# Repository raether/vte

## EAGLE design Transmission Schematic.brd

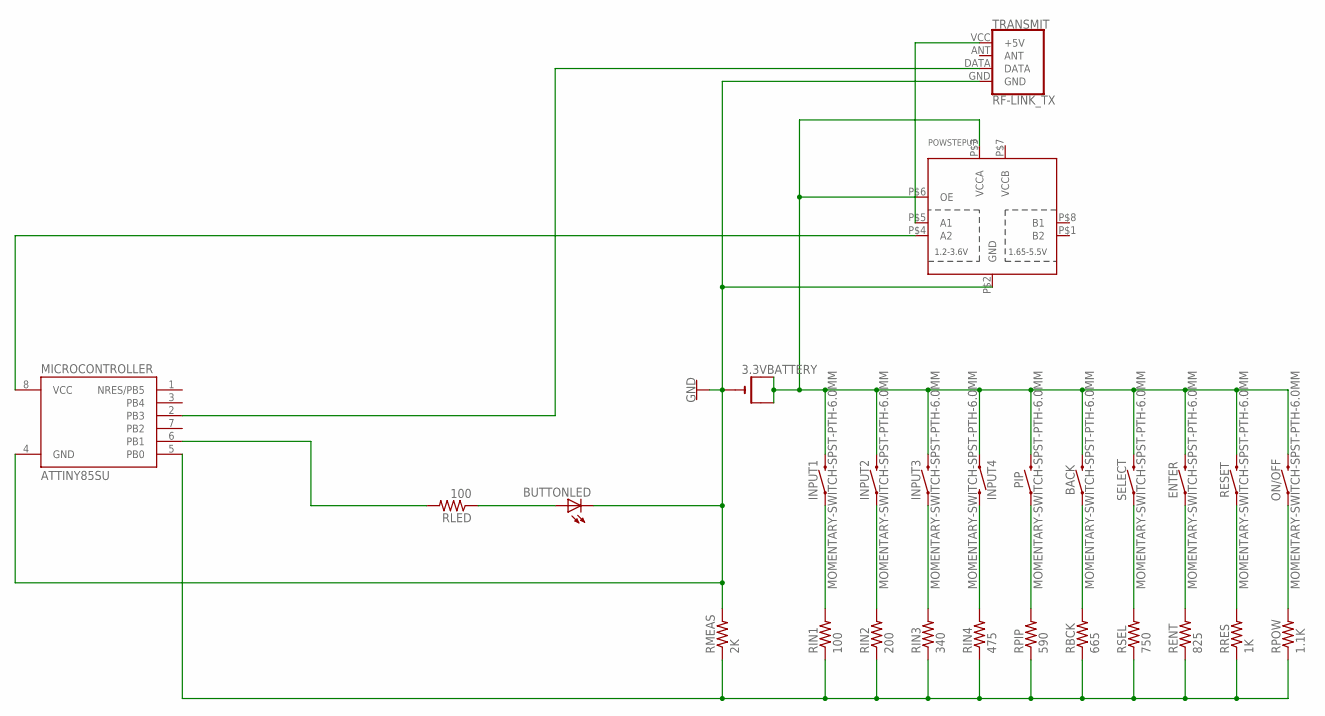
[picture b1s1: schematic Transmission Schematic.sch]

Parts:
3.3VBATTERY: CR1220THM; CR1220-THM
BACK: MOMENTARY-SWITCH-SPST-PTH-6.0MM; TACTILE_SWITCH_PTH_6.0MM
BUTTONLED: LEDCHIPLED_0805; CHIPLED_0805
ENTER: MOMENTARY-SWITCH-SPST-PTH-6.0MM; TACTILE_SWITCH_PTH_6.0MM
INPUT1, INPUT2, INPUT3, INPUT4: MOMENTARY-SWITCH-SPST-PTH-6.0MM; TACTILE_SWITCH_PTH_6.0MM
MICROCONTROLLER: ATTINY85SU; ATTINY85
ON/OFF: MOMENTARY-SWITCH-SPST-PTH-6.0MM; TACTILE_SWITCH_PTH_6.0MM
PIP: MOMENTARY-SWITCH-SPST-PTH-6.0MM; TACTILE_SWITCH_PTH_6.0MM
POWSTEPUP: TXS0102; VFSOP-8
RBCK: 665; R0805
RENT: 825; R0805
RESET: MOMENTARY-SWITCH-SPST-PTH-6.0MM; TACTILE_SWITCH_PTH_6.0MM
RIN1: 100; R0805
RIN2: 200; R0805
RIN3: 340; R0805
RIN4: 475; R0805
RLED: 100; R0805
RMEAS: 2K; R0805
RPIP: 590; R0805
RPOW: 1.1K; R0805
RRES: 1K; R0805
RSEL: 750; R0805
SELECT: MOMENTARY-SWITCH-SPST-PTH-6.0MM; TACTILE_SWITCH_PTH_6.0MM
TRANSMIT: RF-LINK_TX

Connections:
GND: 3.3VBATTERY.-, BUTTONLED.C, MICROCONTROLLER.4 (GND), POWSTEPUP.P$2 (GND), RMEAS.2, TRANSMIT.GND
unnamed: 3.3VBATTERY.+1 (+), 3.3VBATTERY.+2 (+1), BACK.3 (2), ENTER.3 (2), INPUT1.3 (2), INPUT2.3 (2), INPUT3.3 (2), INPUT4.1, ON/OFF.3 (2), PIP.3 (2), POWSTEPUP.P$3 (VCCA), POWSTEPUP.P$6 (OE), RESET.3 (2), SELECT.3 (2)
unnamed: INPUT1.1, RIN1.2
unnamed: INPUT2.1, RIN2.2
unnamed: INPUT3.1, RIN3.2
unnamed: INPUT4.3 (2), RIN4.2
unnamed: PIP.1, RPIP.2
unnamed: BACK.1, RBCK.2
unnamed: RSEL.2, SELECT.1
unnamed: ENTER.1, RENT.2
unnamed: MICROCONTROLLER.5 (PB0), RBCK.1, RENT.1, RIN1.1, RIN2.1, RIN3.1, RIN4.1, RMEAS.1, RPIP.1, RPOW.1, RRES.1, RSEL.1
unnamed: POWSTEPUP.P$5 (A1), TRANSMIT.VCC (+5V)
unnamed: MICROCONTROLLER.8 (VCC), POWSTEPUP.P$4 (A2)
unnamed: RESET.1, RRES.2
unnamed: ON/OFF.1, RPOW.2
unnamed: MICROCONTROLLER.2 (PB3), TRANSMIT.DATA
unnamed: MICROCONTROLLER.6 (PB1), RLED.2
unnamed: BUTTONLED.A, RLED.1

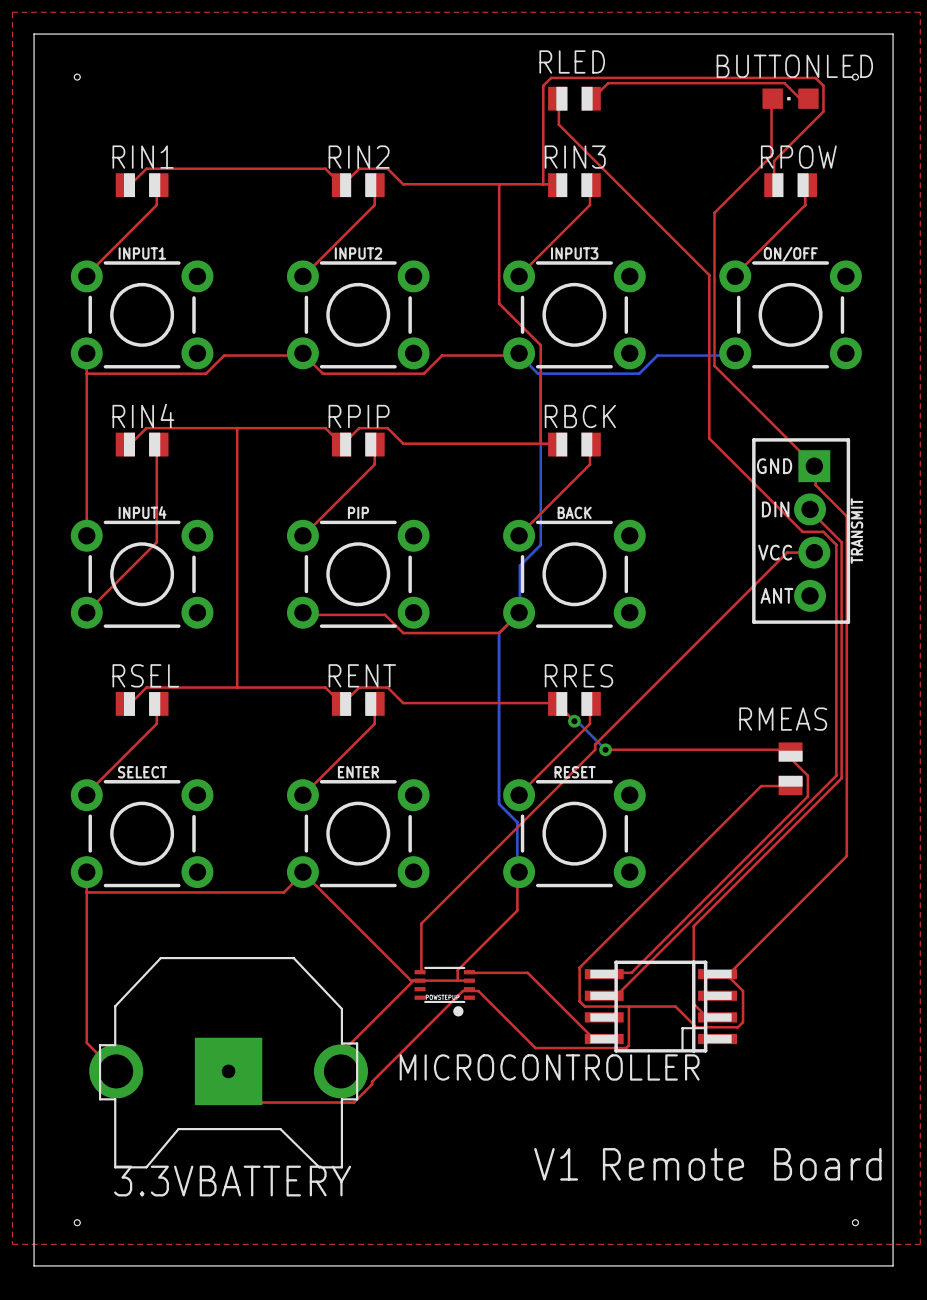
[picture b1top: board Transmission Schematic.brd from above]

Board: 2 copper layers, 50.5 x 72.4 mm, 27 parts (0 on the bottom side), 18 nets.

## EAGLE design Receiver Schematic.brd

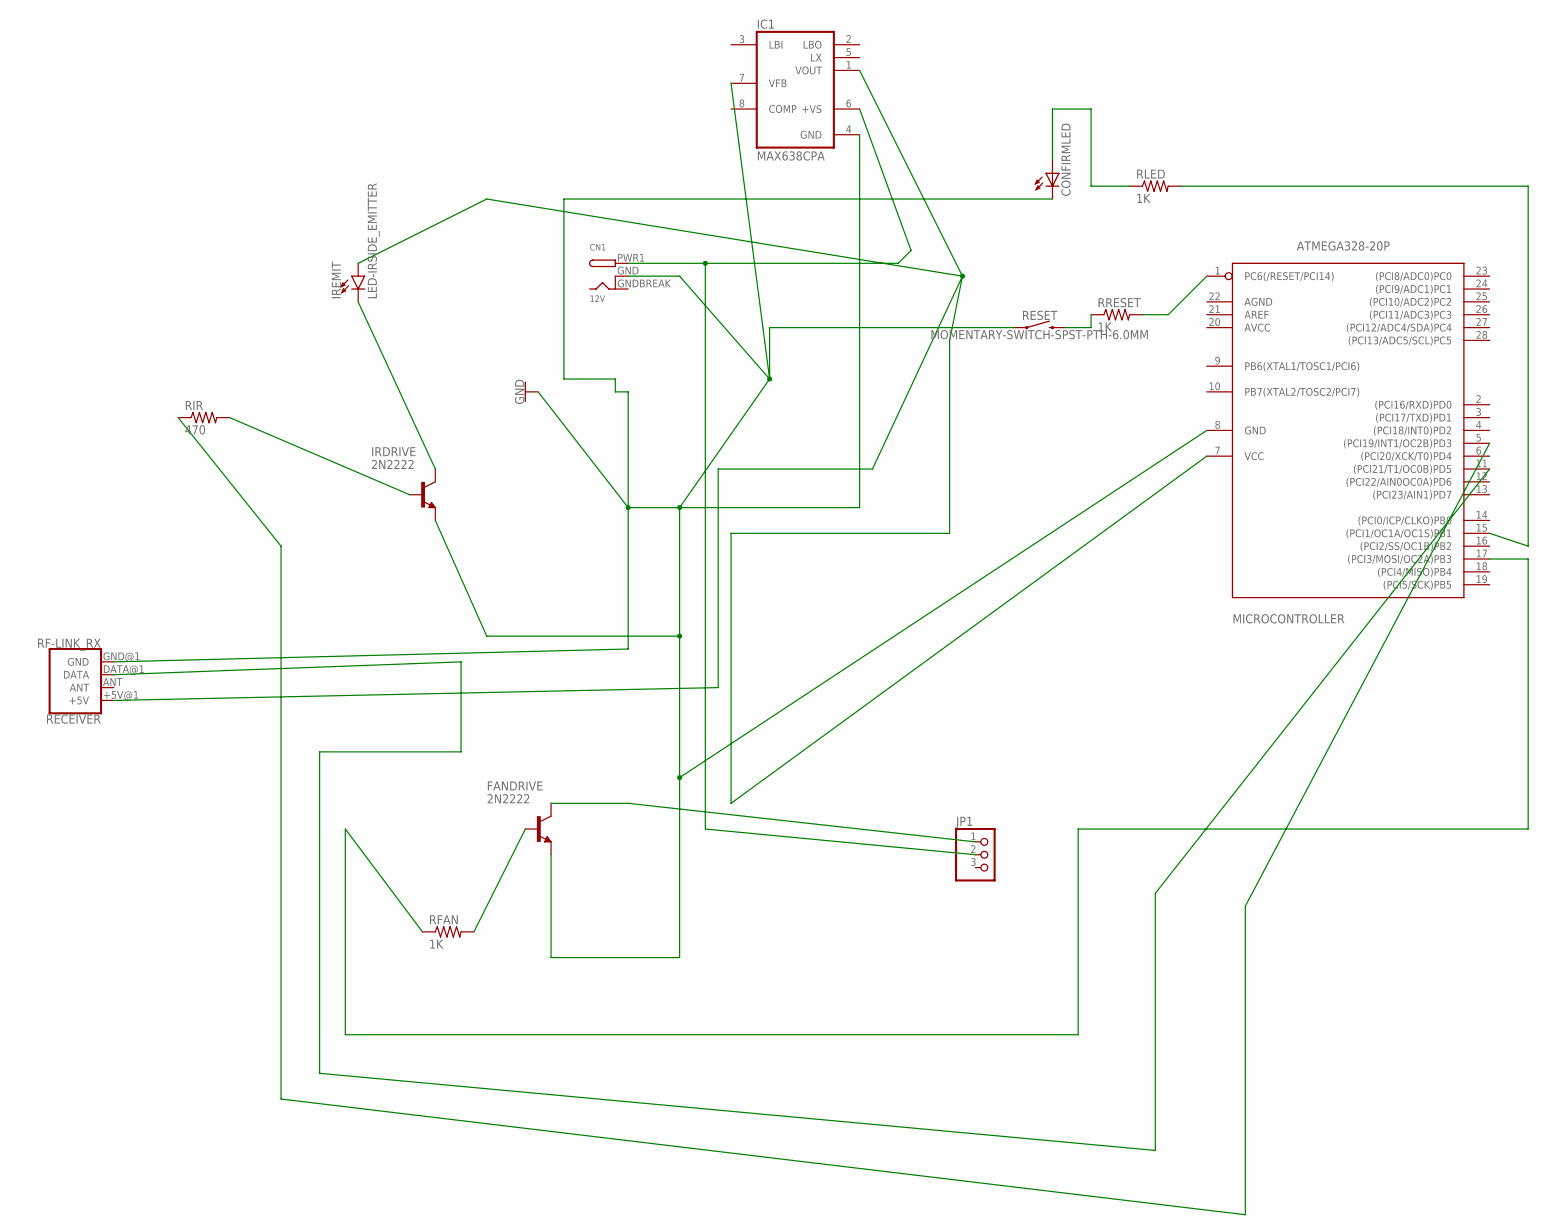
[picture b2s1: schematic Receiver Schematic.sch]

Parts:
CN1: 12V; DCJACK_2MM_SMT
CONFIRMLED: LEDCHIP-LED0805; CHIP-LED0805
FANDRIVE: 2N2222; TO92-EBC-OVAL
IC1: MAX638CPA; DIL08
IRDRIVE: 2N2222; TO92-EBC-OVAL
IREMIT: LED-IRSIDE_EMITTER; LTE-302
JP1: PINHD-1X3; 1X03
MICROCONTROLLER: ATMEGA328-20P; DIL28-3
RECEIVER: RF-LINK_RX
RESET: MOMENTARY-SWITCH-SPST-PTH-6.0MM; TACTILE_SWITCH_PTH_6.0MM
RFAN: 1K; R0805
RIR: 470; R0805
RLED: 1K; R0805
RRESET: 1K; R0805

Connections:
GND: CN1.GND (GNDBREAK), CN1.GNDBREAK (GND), CONFIRMLED.C, FANDRIVE.E, IC1.4 (GND), IC1.7 (VFB), IRDRIVE.E, MICROCONTROLLER.8 (GND), RECEIVER.GND@1 (GND), RESET.1
unnamed: IRDRIVE.C, IREMIT.C
unnamed: CN1.PWR1 (PWR), IC1.6 (+VS), JP1.2
unnamed: MICROCONTROLLER.17 ((PCI3/MOSI/OC2A)PB3), RFAN.1
unnamed: IC1.1 (VOUT), IREMIT.A, MICROCONTROLLER.7 (VCC), RECEIVER.+5V@1 (+5V)
unnamed: FANDRIVE.C, JP1.1
unnamed: IRDRIVE.B, RIR.2
unnamed: FANDRIVE.B, RFAN.2
unnamed: MICROCONTROLLER.15 ((PCI1/OC1A/OC1S)PB1), RLED.2
unnamed: MICROCONTROLLER.5 ((PCI19/INT1/OC2B)PD3), RIR.1
unnamed: MICROCONTROLLER.11 ((PCI21/T1/OC0B)PD5), RECEIVER.DATA@1 (DATA)
unnamed: CONFIRMLED.A, RLED.1
unnamed: RESET.3 (2), RRESET.1
unnamed: MICROCONTROLLER.1 (PC6(/RESET/PCI14)), RRESET.2

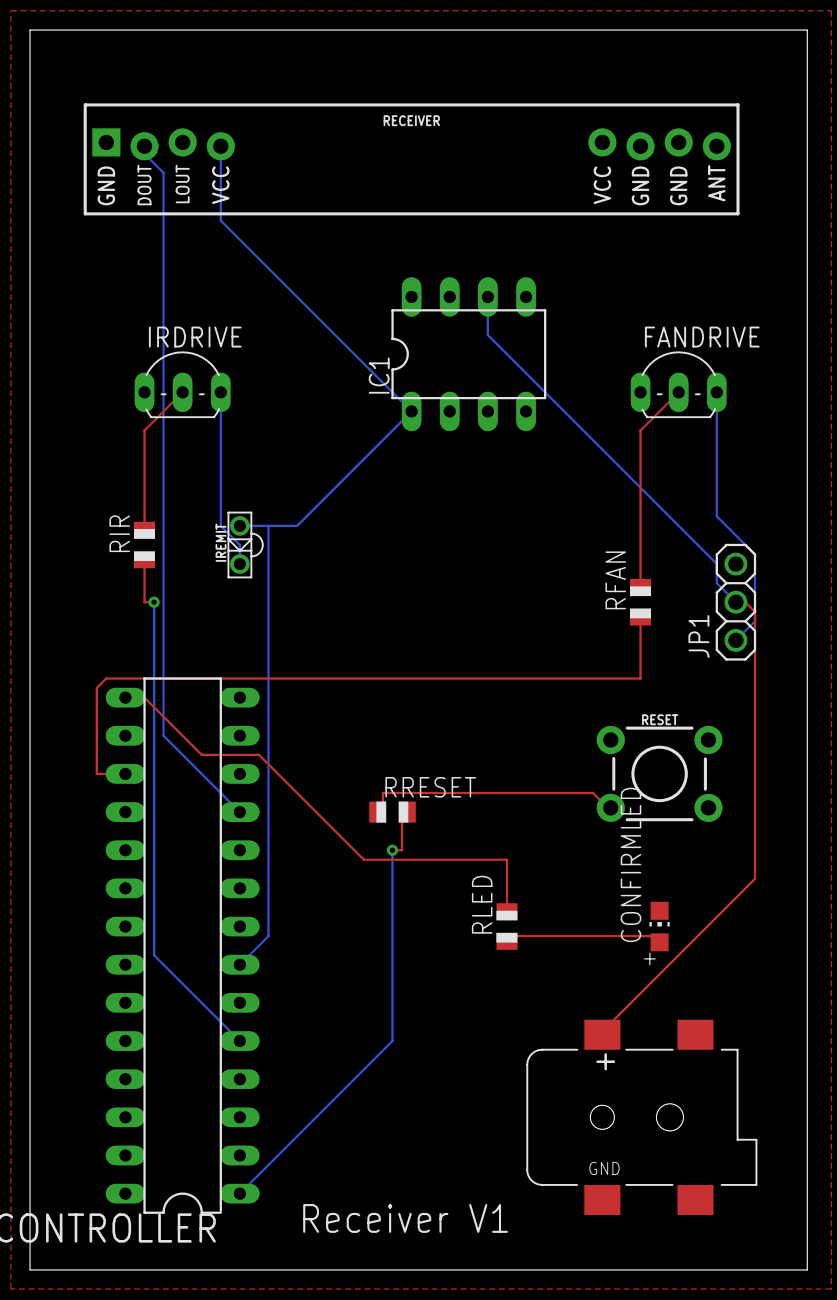
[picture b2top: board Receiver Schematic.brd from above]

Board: 2 copper layers, 51.7 x 82.5 mm, 14 parts (0 on the bottom side), 14 nets.

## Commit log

2017-10-21 Create test

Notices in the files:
parts and their libraries:
SparkFun-LED: Licensing: Creative Commons ShareAlike 4.0 International - https://creativecommons.org/licenses/by-sa/4.0
